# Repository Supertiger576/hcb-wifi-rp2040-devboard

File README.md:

# Wireless RP2040 Devboard

# About 
An RP2040 devboard created with a guide from Hack Club.  It contains a very similar pinout to the Raspberry Pi Pico.  I added the Raspberry Pi RM2 to allow wireless capabilities.

This project interested me as a lot of people have told me that devboards were useful.

# Schematic:

# PCB:

# 3D Model:

Fabrication files are in the devboard folder.  These same files are zipped for import in devboard.zip.

# Necessary Materials

| Id | Designator                          | Footprint                                   | Quantity | Comment                
|----|-------------------------------------|---------------------------------------------|----------|-----------------------------|
| 1  | C1,C10                              | C_0402_1005Metric                           | 2        | 1uF                         |          |     |
| 2  | C2,C3,C4,C5,C6,C7,C8,C9,C11,C12,C17 | C_0402_1005Metric                           | 11       | 0.1uF                       |          |     |
| 3  | C13,C14,C18,C19                     | C_0603_1608Metric                           | 4        | 10uF                        |          |     |
| 4  | C15,C16                             | C_0402_1005Metric                           | 2        | 33pF                        |          |     |
| 5  | J2, J3                              | PinHeader_1x20_P2.54mm_Vertical             | 2        | Conn_01x20                  |          |     |
| 6  | J4                                  | PinHeader_1x03_P2.54mm_Vertical             | 1        | Conn_01x03                  |          |     |
| 7  | R1,R2,R3,R9                         | R_0402_1005Metric                           | 4        | 5.1k                        |          |     |
| 8  | R4,R5                               | R_0402_1005Metric                           | 2        | 27                          |          |     |
| 9  | R6,R7                               | R_0402_1005Metric                           | 2        | 1k                          |          |     |
| 10 | R8,R12                              | R_0402_1005Metric                           | 2        | 10k                         |          |     |
| 11 | R11                                 | R_0402_1005Metric                           | 1        | 470                         |          |     |
| 12 | RM2                                 | RMC20452T                                   | 1        | RM2                         |          |     |
| 13 | SW1                                 | SW_Push_SPST_NO_Alps_SKRK                   | 1        | Button                      |          |     |
| 14 | U1                                  | QFN-56-1EP_7x7mm_P0.4mm_EP3.2x3.2mm         | 1        | RP2040                      |          |     |
| 15 | U2                                  | Winbond_USON-8-1EP_3x2mm_P0.5mm_EP0.2x1.6mm | 1        | Flash Memory                |          |     |
| 16 | U3,U4                               | SOT-23                                      | 2        | Voltage Regulator           |          |     |
| 17 | USB-C Plug                          | USB_C_Plug_JAE_DX07P024AJ1                  | 1        | USB_C_Plug_USB2.0           |          |     |
| 18 | USB-C Receptacle                    | USB_C_Receptacle_HRO_TYPE-C-31-M-12         | 1        | USB_C_Receptacle_USB2.0_14P |          |     |
| 19 | Y1                                  | Crystal_SMD_3225-4Pin_3.2x2.5mm             | 1        | Crystal                     |          |     |

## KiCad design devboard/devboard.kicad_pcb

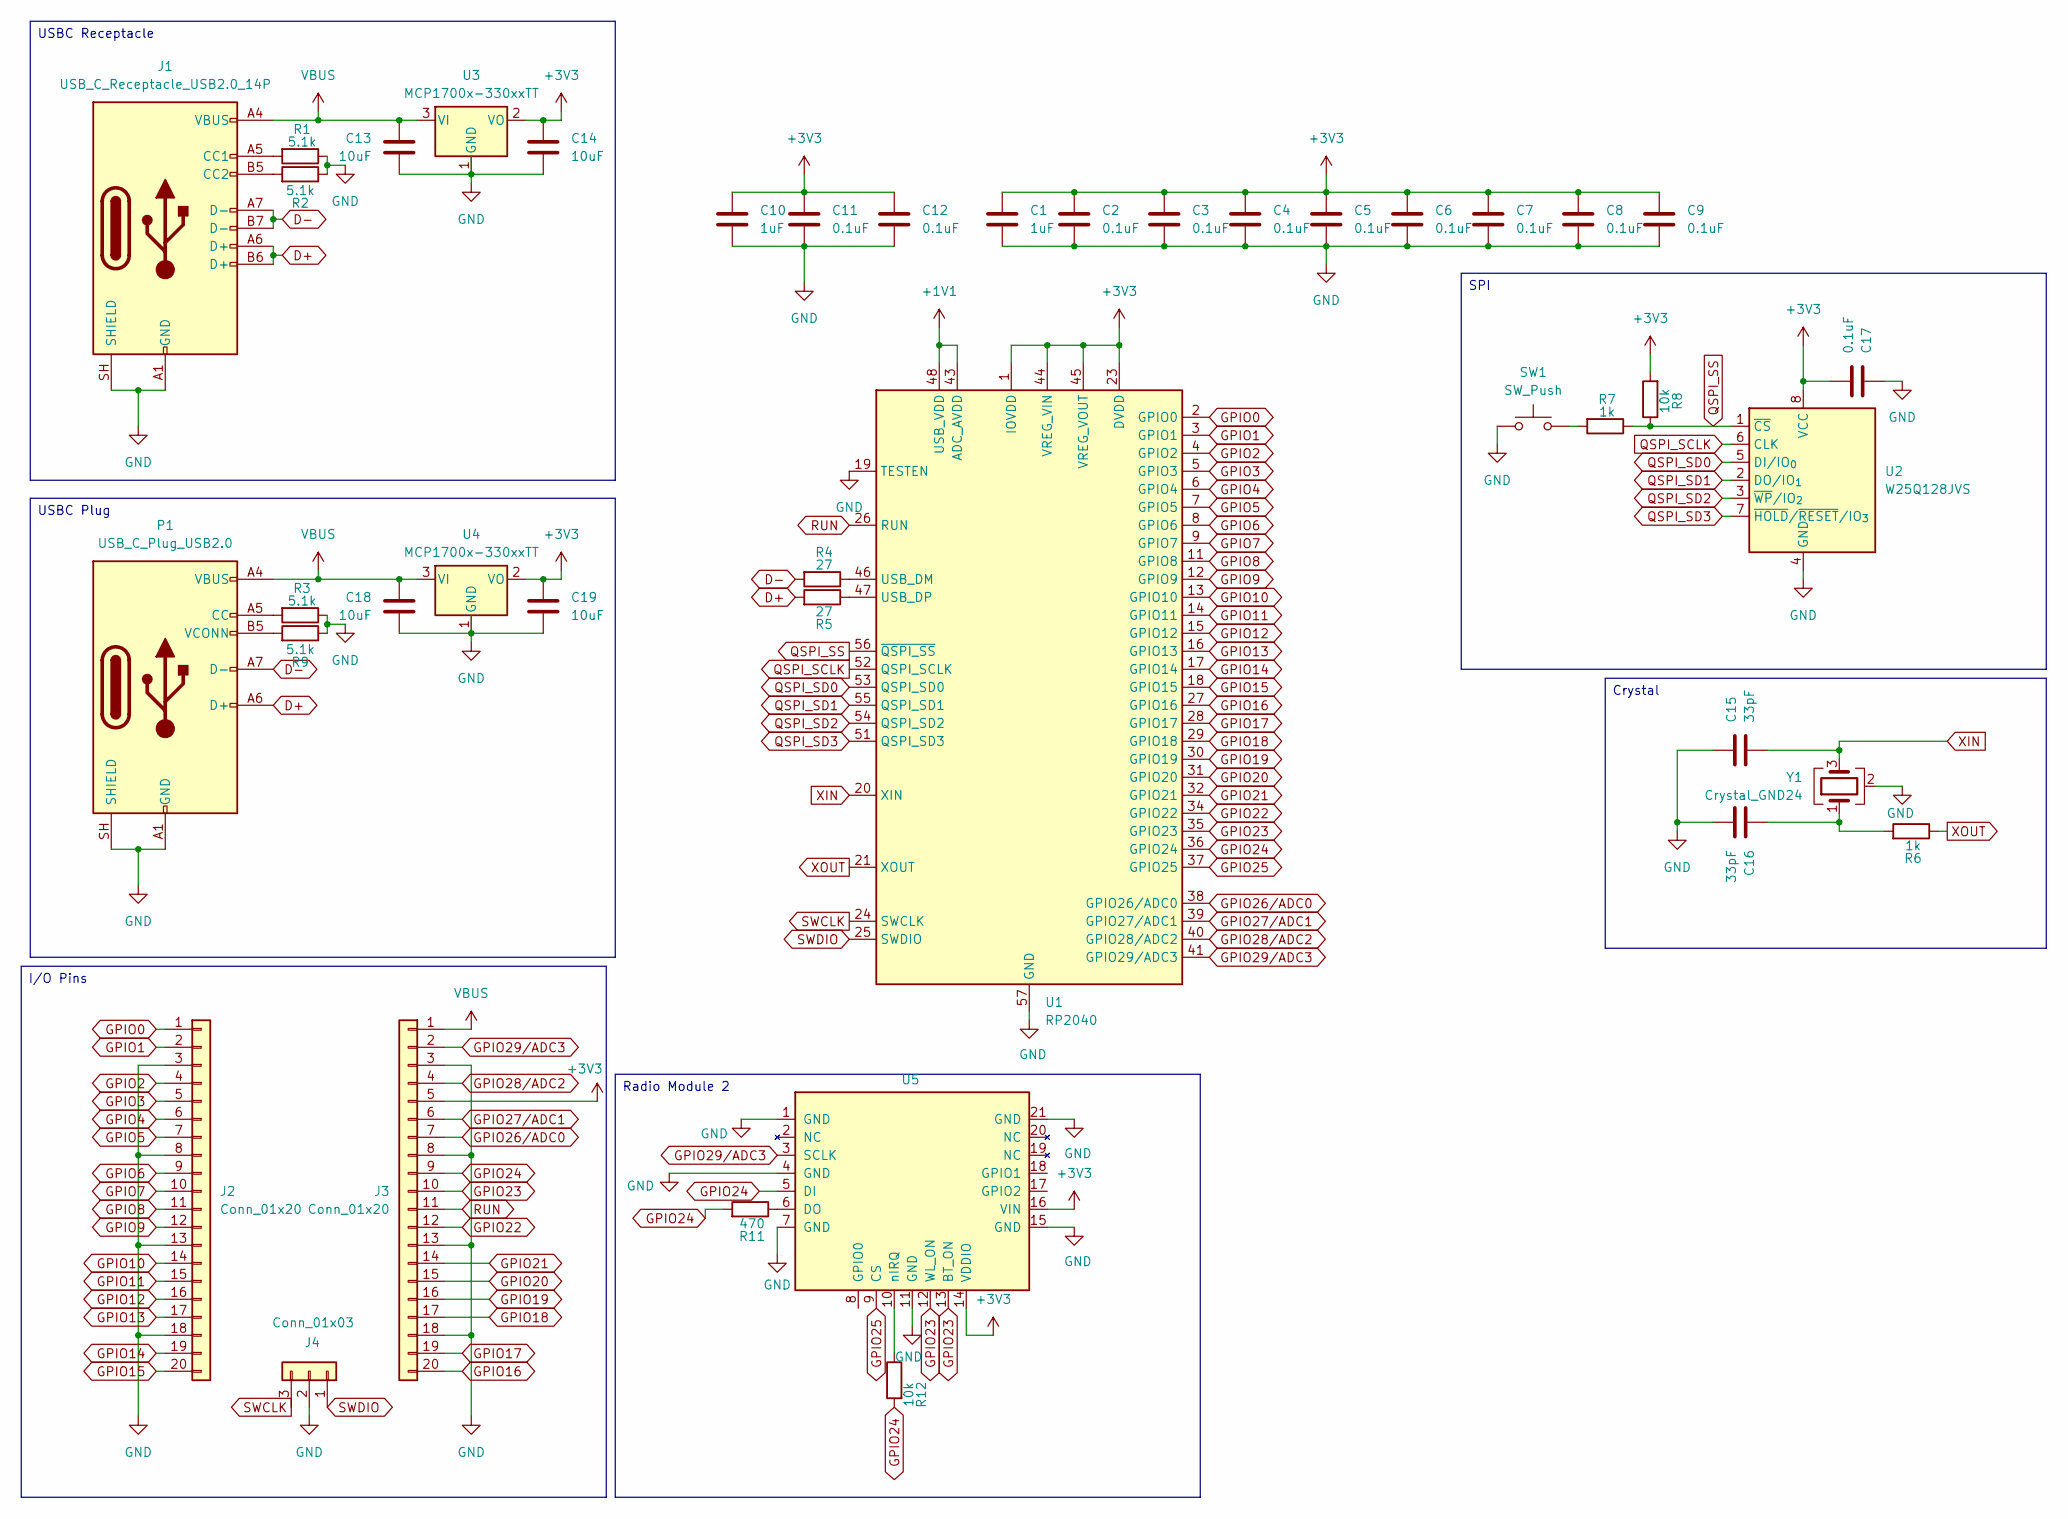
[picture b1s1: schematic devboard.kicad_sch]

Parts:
C1, C10: 1uF; C_0402_1005Metric
C2, C3, C4, C5, C6, C7, C8, C9, C11, C12, C17: 0.1uF; C_0402_1005Metric
C13, C14, C18, C19: 10uF; C_0603_1608Metric
C15, C16: 33pF; C_0402_1005Metric
J1: USB_C_Receptacle_USB2.0_14P; USB_C_Receptacle_HRO_TYPE-C-31-M-12
J2, J3: Conn_01x20; PinHeader_1x20_P2.54mm_Vertical
J4: Conn_01x03; PinHeader_1x03_P2.54mm_Vertical
P1: USB_C_Plug_USB2.0; USB_C_Plug_JAE_DX07P024AJ1
R1, R2, R3, R9: 5.1k; R_0402_1005Metric
R4, R5: 27; R_0402_1005Metric
R6, R7: 1k; R_0402_1005Metric
R8, R12: 10k; R_0402_1005Metric
R11: 470; R_0402_1005Metric
SW1: SW_Push; SW_Push_SPST_NO_Alps_SKRK
U1: RP2040; QFN-56-1EP_7x7mm_P0.4mm_EP3.2x3.2mm
U2: W25Q128JVS; SOIC-8_5.3x5.3mm_P1.27mm
U3, U4: MCP1700x-330xxTT; SOT-23
U5: RM2; RMC20452T
Y1: Crystal_GND24; Crystal_SMD_3225-4Pin_3.2x2.5mm

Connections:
+1V1: U1.43 (ADC_AVDD), U1.48 (USB_VDD)
+3V3: C1.1, C2.1, C3.1, C4.1, C5.1, C6.1, C7.1, C8.1, C9.1, C10.1, C11.1, C12.1, C14.1, C17.2, C19.1, J3.5, R8.2, U1.1 (IOVDD), U1.10 (IOVDD), U1.22 (IOVDD), U1.23 (DVDD), U1.33 (IOVDD), U1.42 (IOVDD), U1.44 (VREG_VIN), U1.45 (VREG_VOUT), U1.49 (IOVDD), U1.50 (DVDD), U2.8 (VCC), U3.2 (VO), U4.2 (VO), U5.14 (VDDIO), U5.16 (VIN); also elsewhere on the board
D+: J1.A6 (D+), J1.B6 (D+), P1.A6 (D+), R5.2; also elsewhere on the board
D-: J1.A7 (D-), J1.B7 (D-), P1.A7 (D-), R4.2; also elsewhere on the board
GND: C1.2, C2.2, C3.2, C4.2, C5.2, C6.2, C7.2, C8.2, C9.2, C10.2, C11.2, C12.2, C13.2, C14.2, C15.1, C16.2, C17.1, C18.2, C19.2, J1.A1 (GND), J1.A12 (GND), J1.B1 (GND), J1.B12 (GND), J1.SH (SHIELD), J2.3, J2.8, J2.13, J2.18, J3.3, J3.8, J3.13, J3.18, J4.2, P1.A1 (GND), P1.A12 (GND), P1.B1 (GND), P1.B12 (GND), P1.SH (SHIELD), R1.1, R2.1, R3.1, R9.1, SW1.1, U1.19 (TESTEN), U1.57 (GND), U2.4 (GND), U3.1 (GND), U4.1 (GND), U5.1 (GND), U5.4 (GND), U5.7 (GND), U5.11 (GND), U5.15 (GND), U5.21 (GND), Y1.2 (G), Y1.4 (G); also elsewhere on the board
GPIO0: J2.1, U1.2 (GPIO0)
GPIO1: J2.2, U1.3 (GPIO1)
GPIO2: J2.4, U1.4 (GPIO2)
GPIO3: J2.5, U1.5 (GPIO3)
GPIO4: J2.6, U1.6 (GPIO4)
GPIO5: J2.7, U1.7 (GPIO5)
GPIO6: J2.9, U1.8 (GPIO6)
GPIO7: J2.10, U1.9 (GPIO7)
GPIO8: J2.11, U1.11 (GPIO8)
GPIO9: J2.12, U1.12 (GPIO9)
GPIO10: J2.14, U1.13 (GPIO10)
GPIO11: J2.15, U1.14 (GPIO11)
GPIO12: J2.16, U1.15 (GPIO12)
GPIO13: J2.17, U1.16 (GPIO13)
GPIO14: J2.19, U1.17 (GPIO14)
GPIO15: J2.20, U1.18 (GPIO15)
GPIO16: J3.20, U1.27 (GPIO16)
GPIO17: J3.19, U1.28 (GPIO17)
GPIO18: J3.17, U1.29 (GPIO18)
GPIO19: J3.16, U1.30 (GPIO19)
GPIO20: J3.15, U1.31 (GPIO20)
GPIO21: J3.14, U1.32 (GPIO21)
GPIO22: J3.12, U1.34 (GPIO22)
GPIO23: J3.10, U1.35 (GPIO23), U5.12 (WL_ON), U5.13 (BT_ON); also elsewhere on the board
GPIO24: J3.9, R11.2, R12.2, U1.36 (GPIO24), U5.5 (DI); also elsewhere on the board
GPIO25: U1.37 (GPIO25), U5.9 (CS); also elsewhere on the board
GPIO26/ADC0: J3.7, U1.38 (GPIO26/ADC0)
GPIO27/ADC1: J3.6, U1.39 (GPIO27/ADC1)
GPIO28/ADC2: J3.4, U1.40 (GPIO28/ADC2)
GPIO29/ADC3: J3.2, U1.41 (GPIO29/ADC3), U5.3 (SCLK); also elsewhere on the board
unnamed: C16.1, R6.2, Y1.1
unnamed 36: J1.A5 (CC1), R1.2; also elsewhere on the board
unnamed 37: J1.B5 (CC2), R2.2; also elsewhere on the board
unnamed 38: P1.A5 (CC), R3.2; also elsewhere on the board
unnamed 39: P1.B5 (VCONN), R9.2; also elsewhere on the board
unnamed: R7.2, SW1.2
unnamed: R4.1, U1.46 (USB_DM)
unnamed: R5.1, U1.47 (USB_DP)
unnamed 43: R11.1, U5.6 (DO); also elsewhere on the board
unnamed 44: R12.1, U5.10 (nIRQ); also elsewhere on the board
QSPI_SCLK: U1.52 (QSPI_SCLK), U2.6 (CLK)
QSPI_SD0: U1.53 (QSPI_SD0), U2.5 (DI/IO_{0})
QSPI_SD1: U1.55 (QSPI_SD1), U2.2 (DO/IO_{1})
QSPI_SD2: U1.54 (QSPI_SD2), U2.3 (~WP/IO_{2})
QSPI_SD3: U1.51 (QSPI_SD3), U2.7 (~HOLD/~RESET/IO_{3})
QSPI_SS: R7.1, R8.1, U1.56 (~QSPI_SS), U2.1 (~CS)
RUN: J3.11, U1.26 (RUN)
SWCLK: J4.3, U1.24 (SWCLK)
SWDIO: J4.1, U1.25 (SWDIO)
VBUS: C13.1, C18.1, J1.A4 (VBUS), J1.A9 (VBUS), J1.B4 (VBUS), J1.B9 (VBUS), J3.1, P1.A4 (VBUS), P1.A9 (VBUS), P1.B4 (VBUS), P1.B9 (VBUS), U3.3 (VI), U4.3 (VI); also elsewhere on the board
XIN: C15.2, U1.20 (XIN), Y1.3
XOUT: R6.1, U1.21 (XOUT)

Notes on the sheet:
Crystal
USBC Receptacle
Radio Module 2
SPI
USBC Plug
I/O Pins

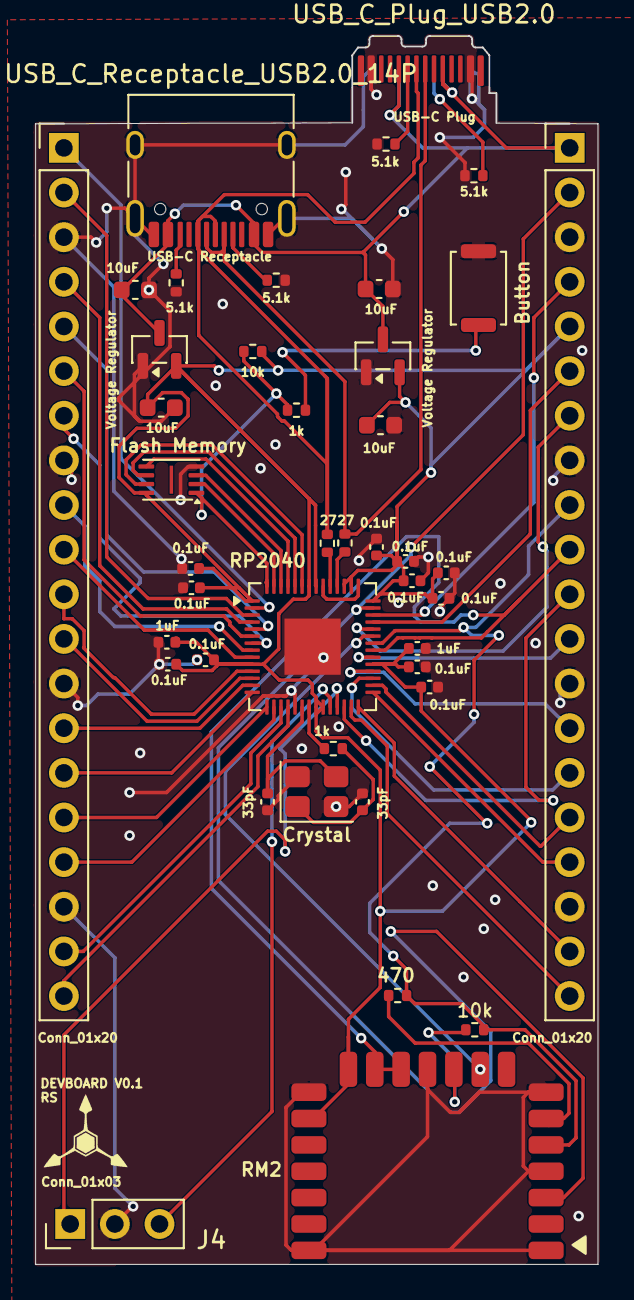
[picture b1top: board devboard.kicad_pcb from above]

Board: 2 copper layers, 32.0 x 69.9 mm, 42 parts (0 on the bottom side), 57 nets.

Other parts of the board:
RM2: RM2; RMC20452T
USB-C Plug: USB_C_Plug_USB2.0; USB_C_Plug_JAE_DX07P024AJ1
USB-C Receptacle: USB_C_Receptacle_USB2.0_14P; USB_C_Receptacle_HRO_TYPE-C-31-M-12

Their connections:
+3V3: RM2.14 (VDDIO), RM2.16 (VIN); also elsewhere on the board
D+: USB-C Plug.A6 (D+), USB-C Receptacle.A6 (D+), USB-C Receptacle.B6 (D+); also elsewhere on the board
D-: USB-C Plug.A7 (D-), USB-C Receptacle.A7 (D-), USB-C Receptacle.B7 (D-); also elsewhere on the board
GND: RM2.1 (GND), RM2.4 (GND), RM2.7 (GND), RM2.11 (GND), RM2.15 (GND), RM2.21 (GND), USB-C Plug.A1 (GND), USB-C Plug.A12 (GND), USB-C Plug.B1 (GND), USB-C Plug.B12 (GND), USB-C Plug.SH (SHIELD), USB-C Receptacle.A1 (GND), USB-C Receptacle.A12 (GND), USB-C Receptacle.B1 (GND), USB-C Receptacle.B12 (GND), USB-C Receptacle.SH (SHIELD); also elsewhere on the board
GPIO23: RM2.12 (WL_ON), RM2.13 (BT_ON); also elsewhere on the board
GPIO24: RM2.5 (DI); also elsewhere on the board
GPIO25: RM2.9 (CS); also elsewhere on the board
GPIO29/ADC3: RM2.3 (SCLK); also elsewhere on the board
unnamed 36: USB-C Receptacle.A5 (CC1); also elsewhere on the board
unnamed 37: USB-C Receptacle.B5 (CC2); also elsewhere on the board
unnamed 38: USB-C Plug.A5 (CC); also elsewhere on the board
unnamed 39: USB-C Plug.B5 (VCONN); also elsewhere on the board
unnamed 43: RM2.6 (DO); also elsewhere on the board
unnamed 44: RM2.10 (nIRQ); also elsewhere on the board
VBUS: USB-C Plug.A4 (VBUS), USB-C Plug.A9 (VBUS), USB-C Plug.B4 (VBUS), USB-C Plug.B9 (VBUS), USB-C Receptacle.A4 (VBUS), USB-C Receptacle.A9 (VBUS), USB-C Receptacle.B4 (VBUS), USB-C Receptacle.B9 (VBUS); also elsewhere on the board
